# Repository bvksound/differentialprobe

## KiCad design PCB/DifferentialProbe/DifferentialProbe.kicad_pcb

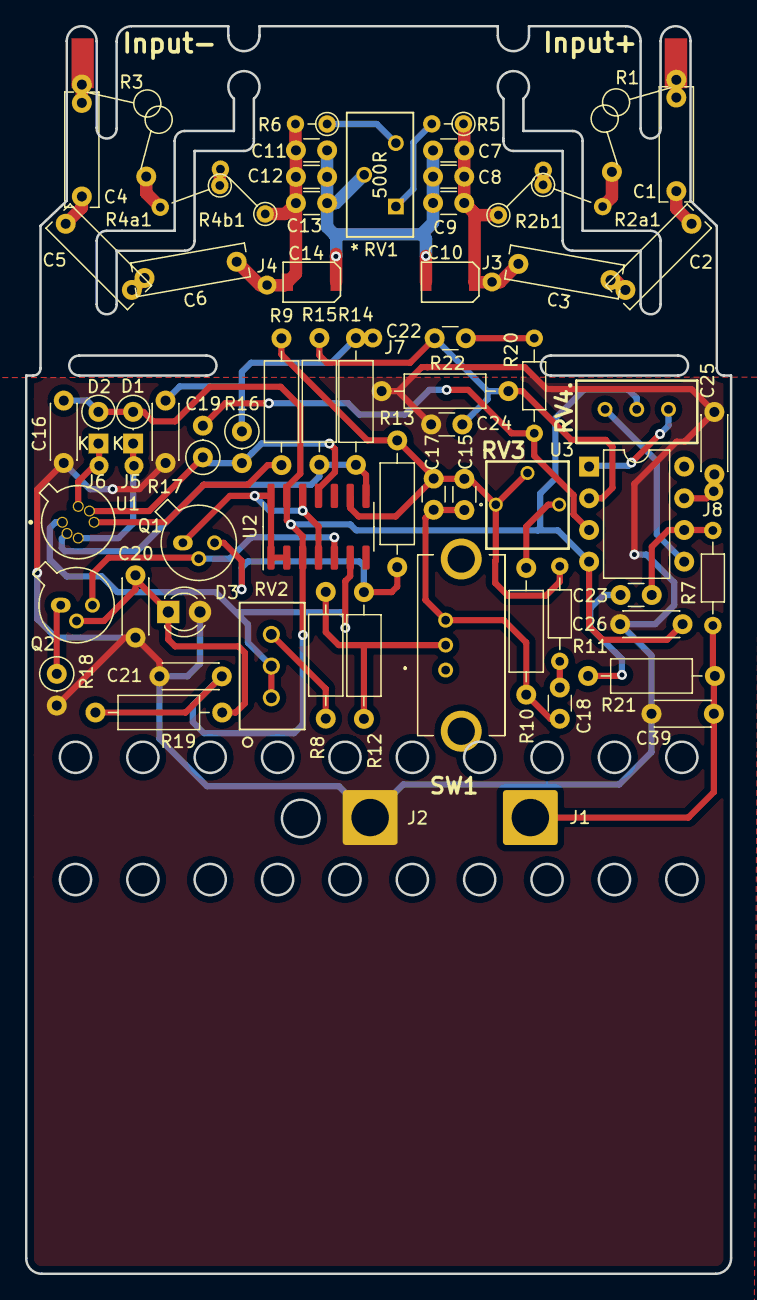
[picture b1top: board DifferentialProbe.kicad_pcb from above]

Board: 2 copper layers, 56.5 x 100.0 mm, 74 parts (0 on the bottom side), 39 nets.

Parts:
C1, C2, C3, C4, C5, C6: 6n8F; C_Rect_L9.0mm_W2.5mm_P7.50mm_MKT
C7, C11: 120pF; C_Disc_D3.0mm_W1.6mm_P2.50mm
C8, C9, C12, C13: 82pF; C_Disc_D3.0mm_W1.6mm_P2.50mm
C10, C14: 8-30pF; JZ300
C15: 22pF; C_Disc_D3.0mm_W1.6mm_P2.50mm
C16, C19, C20, C21, C25, C26: 100nF; C_Disc_D4.3mm_W1.9mm_P5.00mm
C17: 68pF; C_Disc_D3.0mm_W1.6mm_P2.50mm
C18: 33pF; C_Disc_D3.0mm_W1.6mm_P2.50mm
C22: 10nF; C_Disc_D3.0mm_W1.6mm_P2.50mm
C23, C24: 6p8F; C_Disc_D3.0mm_W1.6mm_P2.50mm
C39: Not Fitted; C_Disc_D4.3mm_W1.9mm_P5.00mm
D1, D2: 1N4148; D_DO-35_SOD27_P2.54mm_Vertical_KathodeUp
D3: LED; LED_D3.0mm
J1: Scope Signal; SolderWire-2.5sqmm_1x01_D2.4mm_OD4.4mm
J2: Scope Ground / Screen; SolderWire-2.5sqmm_1x01_D2.4mm_OD4.4mm
J3, J5: Wire A; Wire_Hole
J4, J6: Wire B; Wire_Hole
J7, J8: Wire +9V; Wire_Hole
Probe+1: Pad_Single; PAD_1_8x4mm_Single
Probe-1: Pad_Single; PAD_1_8x4mm_Single
Q1: 2N2222A; TO-18-3
Q2: 2N2907A; TO-18-3
R1, R3: 2M_Series_Resistor; 2M_Series
R2a1, R2b1, R4a1, R4b1: 1M; R_Axial_DIN0204_L3.6mm_D1.6mm_P5.08mm_Vertical
R5, R6: 26K1; R_Axial_DIN0204_L3.6mm_D1.6mm_P2.54mm_Vertical
R7: 7R5; R_Axial_DIN0204_L3.6mm_D1.6mm_P7.62mm_Horizontal
R8: 3K48; R_Axial_DIN0207_L6.3mm_D2.5mm_P10.16mm_Horizontal
R9: 4K02; R_Axial_DIN0207_L6.3mm_D2.5mm_P10.16mm_Horizontal
R10: 374R; R_Axial_DIN0207_L6.3mm_D2.5mm_P10.16mm_Horizontal
R11: 18K; R_Axial_DIN0204_L3.6mm_D1.6mm_P7.62mm_Horizontal
R12, R13: 2K2; R_Axial_DIN0207_L6.3mm_D2.5mm_P10.16mm_Horizontal
R14: 680R; R_Axial_DIN0207_L6.3mm_D2.5mm_P10.16mm_Horizontal
R15: 210R; R_Axial_DIN0207_L6.3mm_D2.5mm_P10.16mm_Horizontal
R16: 680R; R_Axial_DIN0207_L6.3mm_D2.5mm_P2.54mm_Vertical
R17: 210R; R_Axial_DIN0207_L6.3mm_D2.5mm_P2.54mm_Vertical
R18: 620R; R_Axial_DIN0207_L6.3mm_D2.5mm_P2.54mm_Vertical
R19: 6K8; R_Axial_DIN0207_L6.3mm_D2.5mm_P10.16mm_Horizontal
R20: 510R; R_Axial_DIN0204_L3.6mm_D1.6mm_P7.62mm_Horizontal
R21, R22: 4K42; R_Axial_DIN0207_L6.3mm_D2.5mm_P10.16mm_Horizontal
RV1: 500R; T93YB 500K 10&percent_ TU
RV2: 1K; 67WR10KLF
RV3: 500R; 3362P_1
RV4: 100K; 64W_1
SW1: Attenuation Switch; SSSF011700
U1: IFNU411; TO-71
U2: HFA3046BZ; SOIC-14_3.9x8.7mm_P1.27mm
U3: AD797; DIP-8_W7.62mm

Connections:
+9V: C19.1, C25.1, J7.1, J8.1, R14.1, R16.1, U3.7
-9V: C16.2, C21.2, C26.1, D1.2, D2.2, R19.1, RV4.2, U2.3, U2.13, U3.4
GND: C7.1, C8.1, C9.1, C10.2, C11.2, C12.2, C13.2, C14.1, C16.1, C19.2, C20.1, C21.1, C24.1, C25.2, C26.2, C39.2, D3.2, J2.1, R18.2, R22.1, RV1.2
unnamed: C1.1, C2.2
unnamed: C1.2, Probe+1.1, R1.1
unnamed: C2.1, C3.2
unnamed: C4.1, C5.2
unnamed: C4.2, Probe-1.1, R3.1
unnamed: C5.1, C6.2
unnamed: C3.1, C7.2, C8.2, C9.2, C10.1, D1.1, J3.1, J5.1, R2b1.1, R5.1, U1.3
unnamed: C6.1, C11.1, C12.1, C13.1, C14.2, D2.1, J4.1, J6.1, R4b1.1, R6.2, U1.7
unnamed: C15.1, C17.1, C18.1, R10.1, SW1.3
unnamed: C15.2, C17.2, R9.2, R11.2, R13.2, RV3.1, RV3.2, U2.9
unnamed: C18.2, R11.1
unnamed: C20.2, D3.1, Q2.2, R19.2
unnamed: C22.1, R20.1
unnamed: C22.2, C23.1, C24.2, R15.2, R21.1, R22.2, U3.2
unnamed: C23.2, R7.2, U3.6
unnamed: C39.1, J1.1, R7.1, R21.2
unnamed: Q1.1, U2.1, U2.2, U2.4, U2.12, U2.14
unnamed: Q1.2, Q2.3, U2.5
unnamed: Q1.3, R12.1, R13.1
unnamed: Q2.1, R18.1
unnamed: R1.2, R2a1.2
unnamed: R2a1.1, R2b1.2
unnamed: R3.2, R4a1.2
unnamed: R4a1.1, R4b1.2
unnamed: R5.2, RV1.1
unnamed: R6.1, RV1.3
unnamed: R8.1, RV2.3
unnamed: R9.1, U1.5
unnamed: R10.2, RV3.3
unnamed: R8.2, R12.2, SW1.2
unnamed: R14.2, R15.1, U1.2, U2.8
unnamed: R16.2, R17.1, U1.6, U2.11
unnamed: R17.2, R20.2, U3.3
unnamed: RV2.1, RV2.2, U1.1, U2.6
unnamed: RV4.1, U3.5
unnamed: RV4.3, U3.1

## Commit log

2021-05-17 original schematics added
2021-05-17 supporting documents and draft bom added
2021-05-17 Update with descriptions of variable R and C
2021-05-23 draft design and BOM started
2021-05-24 1st design finished
2021-05-27 finalized rev0 for ordering

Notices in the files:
parts and their libraries:
Copyright 2016 Accelerated Designs. All rights reserved.
